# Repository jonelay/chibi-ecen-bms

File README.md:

# Chibi-ECEN-BMS: 7S Lithium-Ion Battery Management System

A 7-cell lithium-ion battery management system designed as a student project for EMEN 5830 (Fundamentals of Systems Engineering) at the University of Colorado Boulder in 2015.

<p align="center">
  
  &nbsp;&nbsp;&nbsp;
  
</p>

## Overview

This BMS was designed for an electric-assist recumbent tricycle with a focus on battery monitoring, safety, and data logging. The design used the ChibiOS operating system, and includes CAN bus communication, microSD data logging, and comprehensive fault detection.

⚠️ **Educational Prototype** - This was a graduate student learning project from 2015 focused on PCB layout techniques for power electronics. While the design is complete and boards were fabricated, this should be considered a learning exercise rather than a production-ready design. Firmware development was not released as part of the project.

## Key Features

- **7S Lithium-Ion Battery Monitoring** - LT6803-based cell voltage monitoring
- **STM32F303 Microcontroller** - ARM Cortex-M4 with floating-point unit
- **Safety Features** - Overcurrent, overvoltage, undervoltage, and thermal protection
- **CAN Bus Interface** - ADM3054 isolated CAN transceiver for vehicle communication
- **Data Logging** - microSD card storage for voltage, current, temperature data
- **Power Management** - LT3990 buck-boost converter for auxiliary power
- **Debug Interface** - JTAG programming and debugging support
- **User Feedback** - RGB status LED, two buttons for user input

## Technical Specifications

- **Battery Configuration**: 7S (7 cells in series)
- **Cell Chemistry**: 18650 Lithium-Ion (Samsung ICR18650-30B, 3000mAh)
- **Voltage Range**: 19.6V - 29.4V (2.8V - 4.2V per cell)
- **Microcontroller**: STM32F303CBT6 (ARM Cortex-M4, 48MHz, 128KB Flash)
- **Battery Monitor**: LT6803-1 (multicell battery stack monitor)
- **Communication**: CAN 2.0B, USB 2.0 (micro-B connector)
- **Data Logging**: microSD card (SPI interface)
- **PCB**: 4-layer board, approximately 100mm x 75mm

See [docs/specifications.md](docs/specifications.md) for complete specifications.

## Systems Engineering Process

This project followed a rigorous systems engineering methodology as taught in EMEN 5830:

1. **Requirements Development** - Stakeholder needs analysis, system requirements derivation
2. **Concept of Operations** - Use cases, operational scenarios, system interactions
3. **Functional Analysis** - 21 iterations of Functional Flow Block Diagrams (FFDB)
4. **Trade Studies** - Component selection based on cost, performance, availability
5. **Design** - Schematic capture, PCB layout, mechanical integration
6. **Testing** - Comprehensive test procedures and validation

The [analysis/](analysis/) directory contains the complete systems engineering documentation, including all 21 FFDB iterations showing the evolution of the design through failure mode analysis.

## Hardware Versions

### Version 1 (v01) - Manufactured & Tested
Version 1 was designed in February 2015, manufactured in March 2015, and tested as part of the course project. Complete gerber files, BOM, and test documentation are included.

- **Status**: Manufactured, assembled, and tested
- **Manufacturing Files**: Complete gerbers available in `hardware/bms-v01/gerbers/`
- **Documentation**: Full schematic, layout, BOM, and test results included

### Version 2 (v02) - Design Iteration
Version 2 was a design iteration that incorporated lessons learned from v01 testing, including corrections to the 8MHz crystal package and expanded AUX power traces. This version was never manufactured and the design files remain in the Eagle source directory.

## Repository Structure

```
chibi-ecen-bms/
├── hardware/              # Manufacturing-ready files (PDFs, gerbers, BOM)
│   └── bms-v01/          # Version 1 (manufactured)
├── design-source/         # Native design files
│   ├── eagle/            # Eagle CAD schematics and layouts
│   ├── cubemx/           # STM32 configuration files
│   └── mechanical/       # SolidWorks models and renders
├── docs/                  # Documentation
├── analysis/              # Systems engineering analysis
│   ├── requirements/     # Requirements documentation
│   ├── failure-analysis/ # FFDB diagrams (21 iterations)
│   ├── calculations/     # Battery and system calculations
│   ├── trade-studies/    # Component selection analysis
│   └── diagrams/         # System block diagrams
├── datasheets/           # Key component datasheets
├── media/                # Photos, renders, and presentation
└── testing/              # Test procedures and results
```

## Getting Started

### Manufacturing

To manufacture this board:

1. Review the [schematic](hardware/bms-v01/bms_v01_schematic.pdf) and [layout](hardware/bms-v01/bms_v01_layout.pdf)
2. Order PCBs using the [gerber files](hardware/bms-v01/gerbers/)
3. Order components from the [BOM](hardware/bms-v01/bms_v01_assembly_bom.csv)
4. Refer to the [test procedure](testing/test-procedure.pdf) for validation

### Modifying the Design

The source Eagle CAD files are in [design-source/eagle/](design-source/eagle/). The STM32 peripheral configuration can be modified using STM32CubeMX with the [.ioc file](design-source/cubemx/bms_v01.ioc).

## Documentation

- **[Specifications](docs/specifications.md)** - System requirements and performance specs
- **[Pinout](docs/pinout.md)** - Connector pinouts and signal definitions
- **[Hardware README](hardware/README.md)** - Manufacturing file details

## Known Issues

Version 1 has two known issues that were addressed in the v02 design:

1. **8MHz Crystal Package** - Incorrect footprint requires rework or substitution
2. **AUX Power Trace** - Undersized trace for auxiliary power distribution

Workarounds: The crystal issue can be resolved by hand-soldering the correct package or using an adapter. The power trace issue can be addressed by adding solder to thicken the trace or adding a parallel wire jumper.

## License

This project is released under the MIT License. See [LICENSE](LICENSE) for details.

Copyright (c) 2015 Jone Lay

You are free to use, modify, and distribute this design for any purpose, with attribution.

## Open Source Hardware

This project is open source hardware. The design files, manufacturing files, and documentation are freely available for educational and non-commercial use.

## Disclaimer

*This project is shared for educational purposes and as a portfolio piece. It was a graduate student project from 2015. While care was taken in the design and the hardware was successfully manufactured and tested, this is not a production-ready design. Use at your own risk. Battery management systems must be designed with extreme care for safety - this design is presented for educational purposes only.

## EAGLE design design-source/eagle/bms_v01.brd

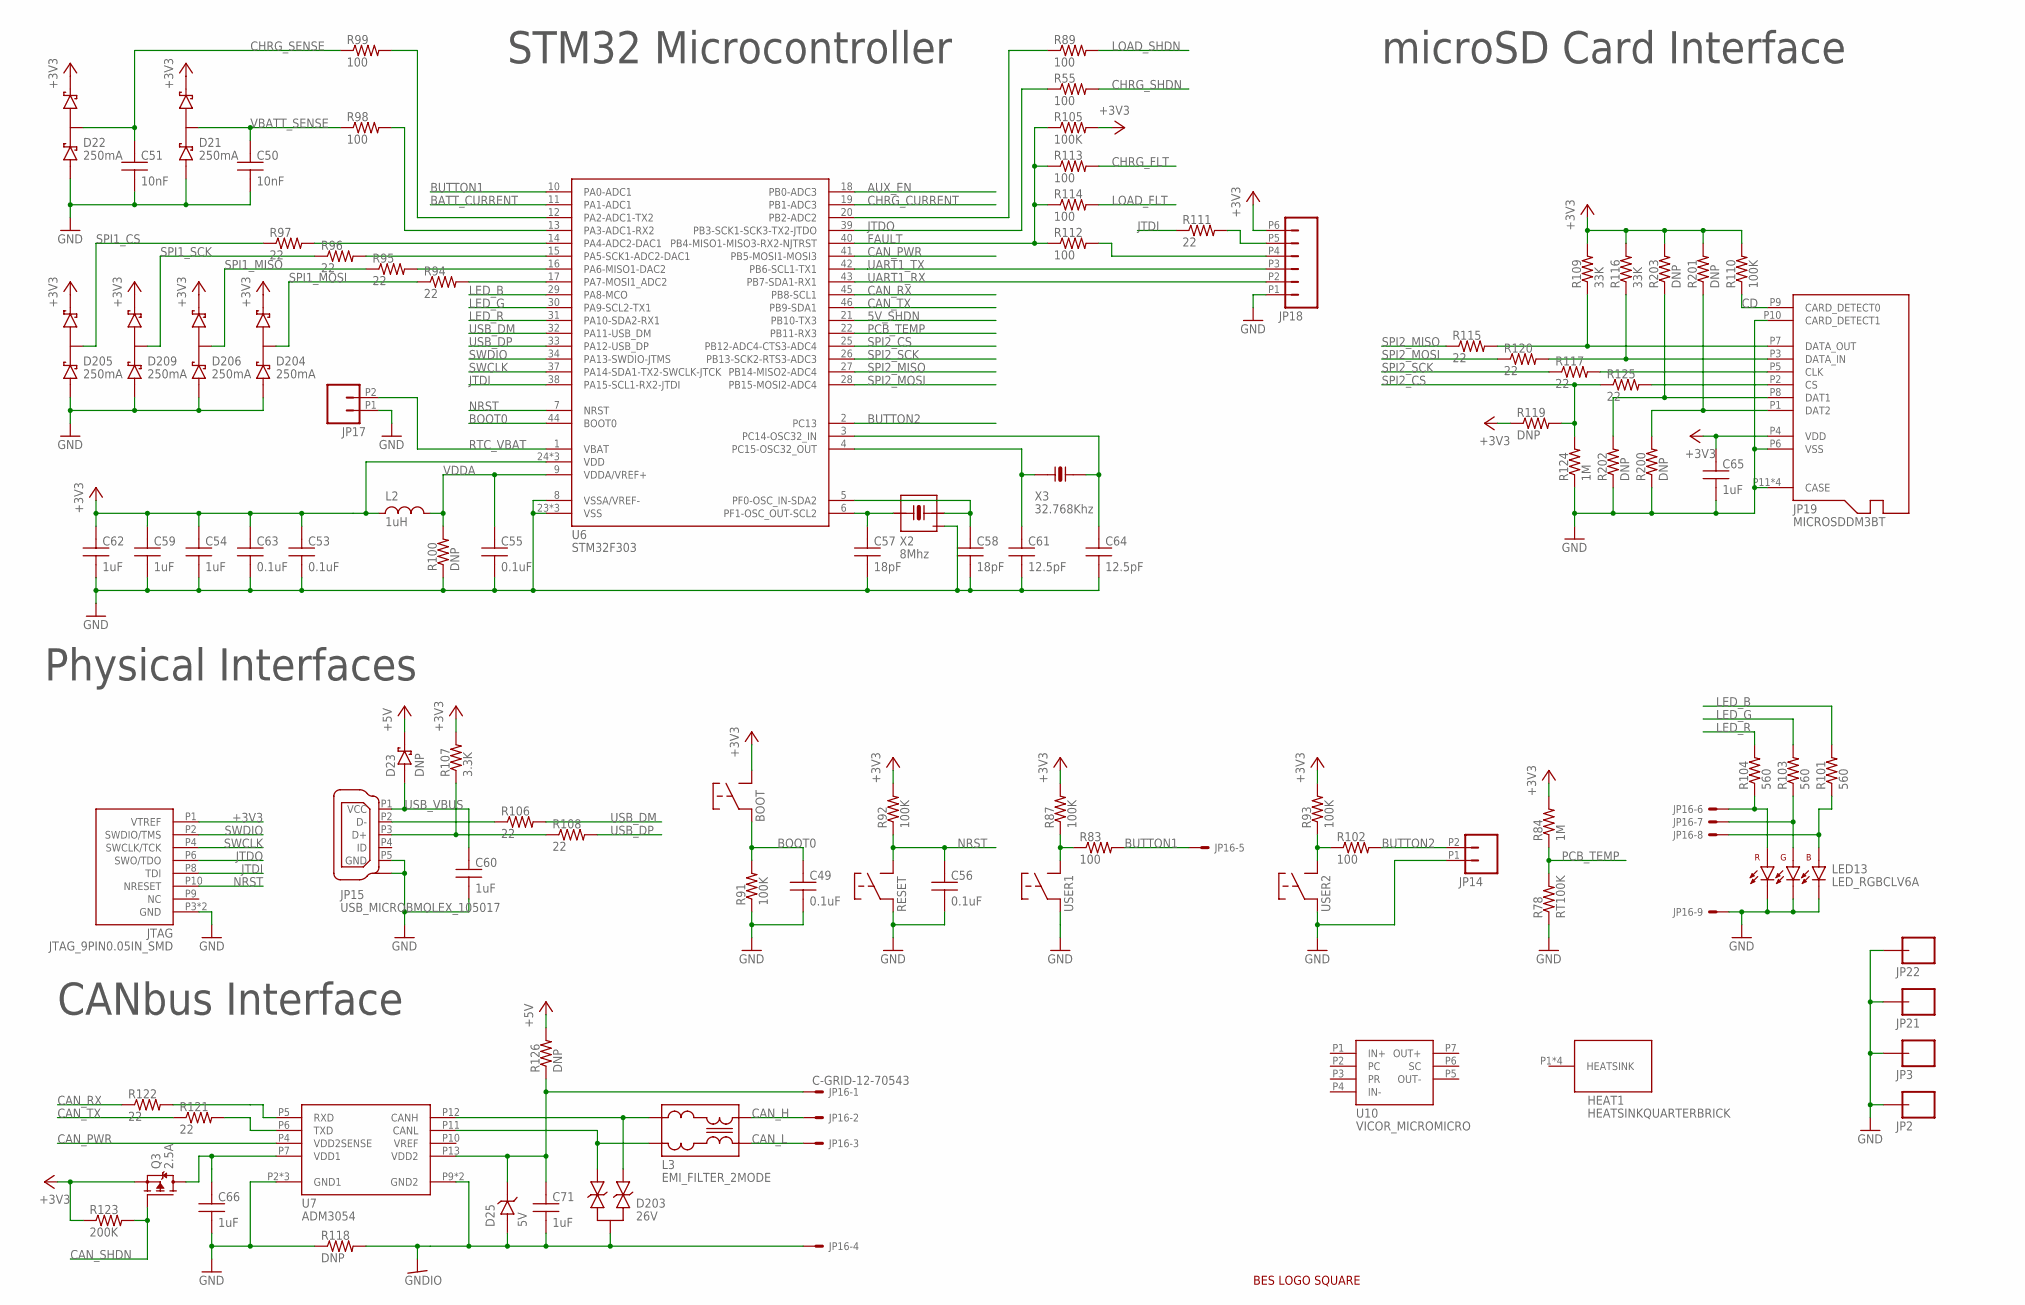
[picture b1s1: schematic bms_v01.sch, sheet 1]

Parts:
BOOT: SWITCH_MOMENTEVQP2; MOMENTARY_SW_EVQP2
C49, C53, C55, C56, C63: 0.1uF; 0603_SILK
C50, C51: 10nF; 0603_SILK
C54, C59, C60, C62, C65, C66, C71: 1uF; 0603_SILK
C57, C58: 18pF; 0603_SILK
C61, C64: 12.5pF; 0603_SILK
D21, D22, D204, D205, D206, D209: 250mA; SOT23
D23: DNP; SOT23
D25: 5V; SOT23
D203: 26V; SOT23
HEAT1: HEATSINKQUARTERBRICK; HEATSINK_BRICK_QUARTER
JP2, JP3, JP21, JP22: CONNECTOR-1PIN3.5MM; HOLE_3.5MM
JP14: HEADER-2PIN2MM; HEADER_2MM_2PIN
JP15: USB_MICROBMOLEX_105017; USB-MICRO-B-MOLEX_105017
JP16: C-GRID-12-70543; 70543-12
JP17: HEADER-2PIN0.05IN; HEADER-SMALL-2PIN00.05IN
JP18: HEADER-6PIN2MM; HEADER_2MM_6PIN
JP19: MICROSDDM3BT; MICROSD_DM3BT
JTAG: JTAG_9PIN0.05IN_SMD; JTAG_9PIN_0.05IN_SMD
L2: 1uH; 0603_SILK
L3: EMI_FILTER_2MODE; FILTER_EXC24CX
LED13: LED_RGBCLV6A; RGB_LED_CLV6A
LOGO1: LOGOSILK_0.325IN; LOGO_SILK_0.325IN
Q3: 2.5A; SOT23
R55, R83, R89, R98, R99, R102, R112, R113, R114: 100; 0603_SILK
R78: RT100K; 0603_SILK
R84, R124: 1M; 0603_SILK
R87, R91, R92, R93, R105, R110: 100K; 0603_SILK
R94, R95, R96, R97, R106, R108, R111, R115, R117, R120, R121, R122, R125: 22; 0603_SILK
R100, R118, R119, R126, R200, R201, R202, R203: DNP; 0603_SILK
R101, R103, R104: 560; 0603_SILK
R107: 3.3K; 0603_SILK
R109, R116: 33K; 0603_SILK
R123: 200K; 0603_SILK
RESET: SWITCH_MOMENTEVQP2; MOMENTARY_SW_EVQP2
U6: STM32F303; TQFP48
U7: ADM3054; SOIC-16_W_ANALOG
U10: VICOR_MICROMICRO; VICOR_QUARTER
USER1, USER2: SWITCH_MOMENTEVQP2; MOMENTARY_SW_EVQP2
X2: 8Mhz; ABRACOM_CLOCK
X3: 32.768Khz; ABS07

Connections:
5V_SHDN: U6.21 (PB10-TX3); also elsewhere on the board
+3V3: BOOT.P2, BOOT.P4 (P2), C53.P1 (1), C54.P1 (1), C59.P1 (1), C62.P1 (1), C63.P1 (1), C65.P1 (1), D21.2 (C), D22.2 (C), D204.2 (C), D205.2 (C), D206.2 (C), D209.2 (C), JP18.P6, JP19.P4 (VDD), JTAG.P1 (VTREF), L2.P1 (1), Q3.2 (S), R84.P2 (2), R87.P2 (2), R92.P2 (2), R93.P2 (2), R105.P2 (2), R107.P2 (2), R109.P2 (2), R110.P2 (2), R116.P2 (2), R119.P1 (1), R123.P1 (1), R201.P2 (2), R203.P2 (2), U6.24 (VDD), U6.36 (VDD), U6.48 (VDD); also elsewhere on the board
+5V: D23.3 (C), R126.P2 (2); also elsewhere on the board
AUX_EN: U6.18 (PB0-ADC3); also elsewhere on the board
BATT_CURRENT: U6.11 (PA1-ADC1); also elsewhere on the board
BOOT0: BOOT.P1, BOOT.P3 (P1), C49.P1 (1), R91.P2 (2), U6.44 (BOOT0)
BUTTON1: JP16.5, R83.P2 (2), U6.10 (PA0-ADC1)
BUTTON2: JP14.P2, R102.P2 (2), U6.2 (PC13)
CAN_H: JP16.2, L3.P4 (4)
CAN_L: JP16.3, L3.P3 (3)
CAN_PWR: U6.41 (PB5-MOSI1-MOSI3), U7.P4 (VDD2SENSE)
CAN_RX: R122.P1 (1), U6.45 (PB8-SCL1)
CAN_SHDN: Q3.1 (G), R123.P2 (2); also elsewhere on the board
CAN_TX: R121.P1 (1), U6.46 (PB9-SDA1)
CAN_VDD: C71.P1 (1), D25.3 (C), JP16.1, R126.P1 (1), U7.P13 (VDD2)
CD: JP19.P9 (CARD_DETECT0), R110.P1 (1)
CHRG_CURRENT: U6.19 (PB1-ADC3); also elsewhere on the board
CHRG_FLT: R113.P2 (2); also elsewhere on the board
CHRG_SENSE: C51.P1 (1), D22.3 (MID), R99.P1 (1); also elsewhere on the board
CHRG_SHDN: R55.P2 (2); also elsewhere on the board
FAULT: R105.P1 (1), R112.P1 (1), R113.P1 (1), R114.P1 (1), U6.40 (PB4-MISO1-MISO3-RX2-NJTRST)
GND: C49.P2 (2), C50.P2 (2), C51.P2 (2), C53.P2 (2), C54.P2 (2), C55.P2 (2), C56.P2 (2), C57.P2 (2), C58.P2 (2), C59.P2 (2), C60.P2 (2), C61.P2 (2), C62.P2 (2), C63.P2 (2), C64.P2 (2), C65.P2 (2), C66.P2 (2), D21.1 (A), D22.1 (A), D204.1 (A), D205.1 (A), D206.1 (A), D209.1 (A), JP2.P$1, JP3.P$1, JP14.P1, JP15.P5 (GND), JP15.PAD1 (CASE), JP15.PAD2 (CASE), JP15.PAD3 (CASE), JP15.PAD3-HOLE (CASE), JP15.PAD4 (CASE), JP15.PAD4-HOLE (CASE), JP15.THRUPAD1 (CASE), JP15.THRUPAD2 (CASE), JP16.9, JP17.P1, JP18.P1, JP19.P6 (VSS), JP19.P10 (CARD_DETECT1), JP19.P11 (CASE), JP19.P12 (CASE), JP19.P13 (CASE), JP19.P14 (CASE), JP21.P$1, JP22.P$1, JTAG.P3 (GND), JTAG.P5 (GND), LED13.1 (BC), LED13.2 (GC), LED13.3 (RC), R78.P1 (1), R91.P1 (1), R100.P1 (1), R118.P1 (1), R124.P1 (1), R200.P1 (1), R202.P1 (1), RESET.P1, RESET.P3 (P1), U6.8 (VSSA/VREF-), U6.23 (VSS), U6.35 (VSS), U6.47 (VSS), U7.P2 (GND1), U7.P3 (GND1), U7.P8 (GND1), USER1.P1, USER1.P3 (P1), USER2.P1, USER2.P3 (P1), X2.2 (CASE), X2.4 (CASE); also elsewhere on the board
GNDIO: C71.P2 (2), D25.1 (A), D203.3 (C1), JP16.4, R118.P2 (2), U7.P9 (GND2), U7.P16 (GND2)
JTDI: JTAG.P8 (TDI), R111.P1 (1), U6.38 (PA15-SCL1-RX2-JTDI)
JTDO: JTAG.P6 (SWO/TDO), R55.P1 (1), U6.39 (PB3-SCK1-SCK3-TX2-JTDO)
LED_B: R101.P2 (2), U6.29 (PA8-MCO)
LED_G: R103.P2 (2), U6.30 (PA9-SCL2-TX1)
LED_R: R104.P2 (2), U6.31 (PA10-SDA2-RX1)
LOAD_FLT: R114.P2 (2); also elsewhere on the board
LOAD_SHDN: R89.P2 (2); also elsewhere on the board
unnamed: C66.P1 (1), Q3.3 (D), U7.P7 (VDD1)
unnamed: D203.1 (A), L3.P2 (2), U7.P11 (CANL)
unnamed: R99.P2 (2), U6.12 (PA2-ADC1-TX2)
unnamed: R83.P1 (1), R87.P1 (1), USER1.P2, USER1.P4 (P2)
unnamed: JP15.P2 (D-), R106.P1 (1)
unnamed: R93.P1 (1), R102.P1 (1), USER2.P2, USER2.P4 (P2)
unnamed: R89.P1 (1), U6.20 (PB2-ADC2)
unnamed: R98.P2 (2), U6.13 (PA3-ADC1-RX2)
unnamed: C58.P1 (1), U6.5 (PF0-OSC_IN-SDA2), X2.3 (3A)
unnamed: JP15.P3 (D+), R107.P1 (1), R108.P1 (1)
unnamed: R94.P2 (2), U6.17 (PA7-MOSI1_ADC2)
unnamed: R95.P2 (2), U6.16 (PA6-MISO1-DAC2)
unnamed: C57.P1 (1), U6.6 (PF1-OSC_OUT-SCL2), X2.1 (1A)
unnamed: R96.P2 (2), U6.15 (PA5-SCK1-ADC2-DAC1)
unnamed: JP19.P1 (DAT2), R200.P2 (2), R201.P1 (1)
unnamed: JP19.P8 (DAT1), R202.P2 (2), R203.P1 (1)
unnamed: JP19.P3 (DATA_IN), R116.P1 (1), R120.P2 (2)
unnamed: JP19.P7 (DATA_OUT), R109.P1 (1), R115.P2 (2)
unnamed: D203.2 (A1), L3.P1 (1), U7.P12 (CANH)
unnamed: R121.P2 (2), U7.P6 (TXD)
unnamed: R122.P2 (2), U7.P5 (RXD)
unnamed: R97.P2 (2), U6.14 (PA4-ADC2-DAC1)
unnamed: C61.P1 (1), U6.4 (PC15-OSC32_OUT), X3.P1 (1A)
unnamed: C64.P1 (1), U6.3 (PC14-OSC32_IN), X3.P2 (3A)
unnamed: JP18.P4, R112.P2 (2)
unnamed: JP18.P5, R111.P2 (2)
unnamed: JP19.P5 (CLK), R117.P2 (2)
unnamed: JP19.P2 (CS), R125.P2 (2)
unnamed: JP16.6, LED13.4 (RA), R104.P1 (1)
unnamed: JP16.7, LED13.5 (GA), R103.P1 (1)
unnamed: JP16.8, LED13.6 (BA), R101.P1 (1)
NRST: C56.P1 (1), JTAG.P10 (NRESET), R92.P1 (1), RESET.P2, RESET.P4 (P2), U6.7 (NRST)
PCB_TEMP: R78.P2 (2), R84.P1 (1), U6.22 (PB11-RX3)
RTC_VBAT: JP17.P2, U6.1 (VBAT)
SPI1_CS: D205.3 (MID), R97.P1 (1); also elsewhere on the board
SPI1_MISO: D206.3 (MID), R95.P1 (1); also elsewhere on the board
SPI1_MOSI: D204.3 (MID), R94.P1 (1); also elsewhere on the board
SPI1_SCK: D209.3 (MID), R96.P1 (1); also elsewhere on the board
SPI2_CS: R119.P2 (2), R124.P2 (2), R125.P1 (1), U6.25 (PB12-ADC4-CTS3-ADC4)
SPI2_MISO: R115.P1 (1), U6.27 (PB14-MISO2-ADC4)
SPI2_MOSI: R120.P1 (1), U6.28 (PB15-MOSI2-ADC4)
SPI2_SCK: R117.P1 (1), U6.26 (PB13-SCK2-RTS3-ADC3)
SWCLK: JTAG.P4 (SWCLK/TCK), U6.37 (PA14-SDA1-TX2-SWCLK-JTCK)
SWDIO: JTAG.P2 (SWDIO/TMS), U6.34 (PA13-SWDIO-JTMS)
UART1_RX: JP18.P2, U6.43 (PB7-SDA1-RX1)
UART1_TX: JP18.P3, U6.42 (PB6-SCL1-TX1)
USB_DM: R106.P2 (2), U6.32 (PA11-USB_DM)
USB_DP: R108.P2 (2), U6.33 (PA12-USB_DP)
USB_VBUS: C60.P1 (1), D23.1 (A), JP15.P1 (VCC)
VBATT_SENSE: C50.P1 (1), D21.3 (MID), R98.P1 (1); also elsewhere on the board
VDDA: C55.P1 (1), L2.P2 (2), R100.P2 (2), U6.9 (VDDA/VREF+)

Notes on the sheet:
CANbus Interface
STM32 Microcontroller
microSD Card Interface
Physical Interfaces

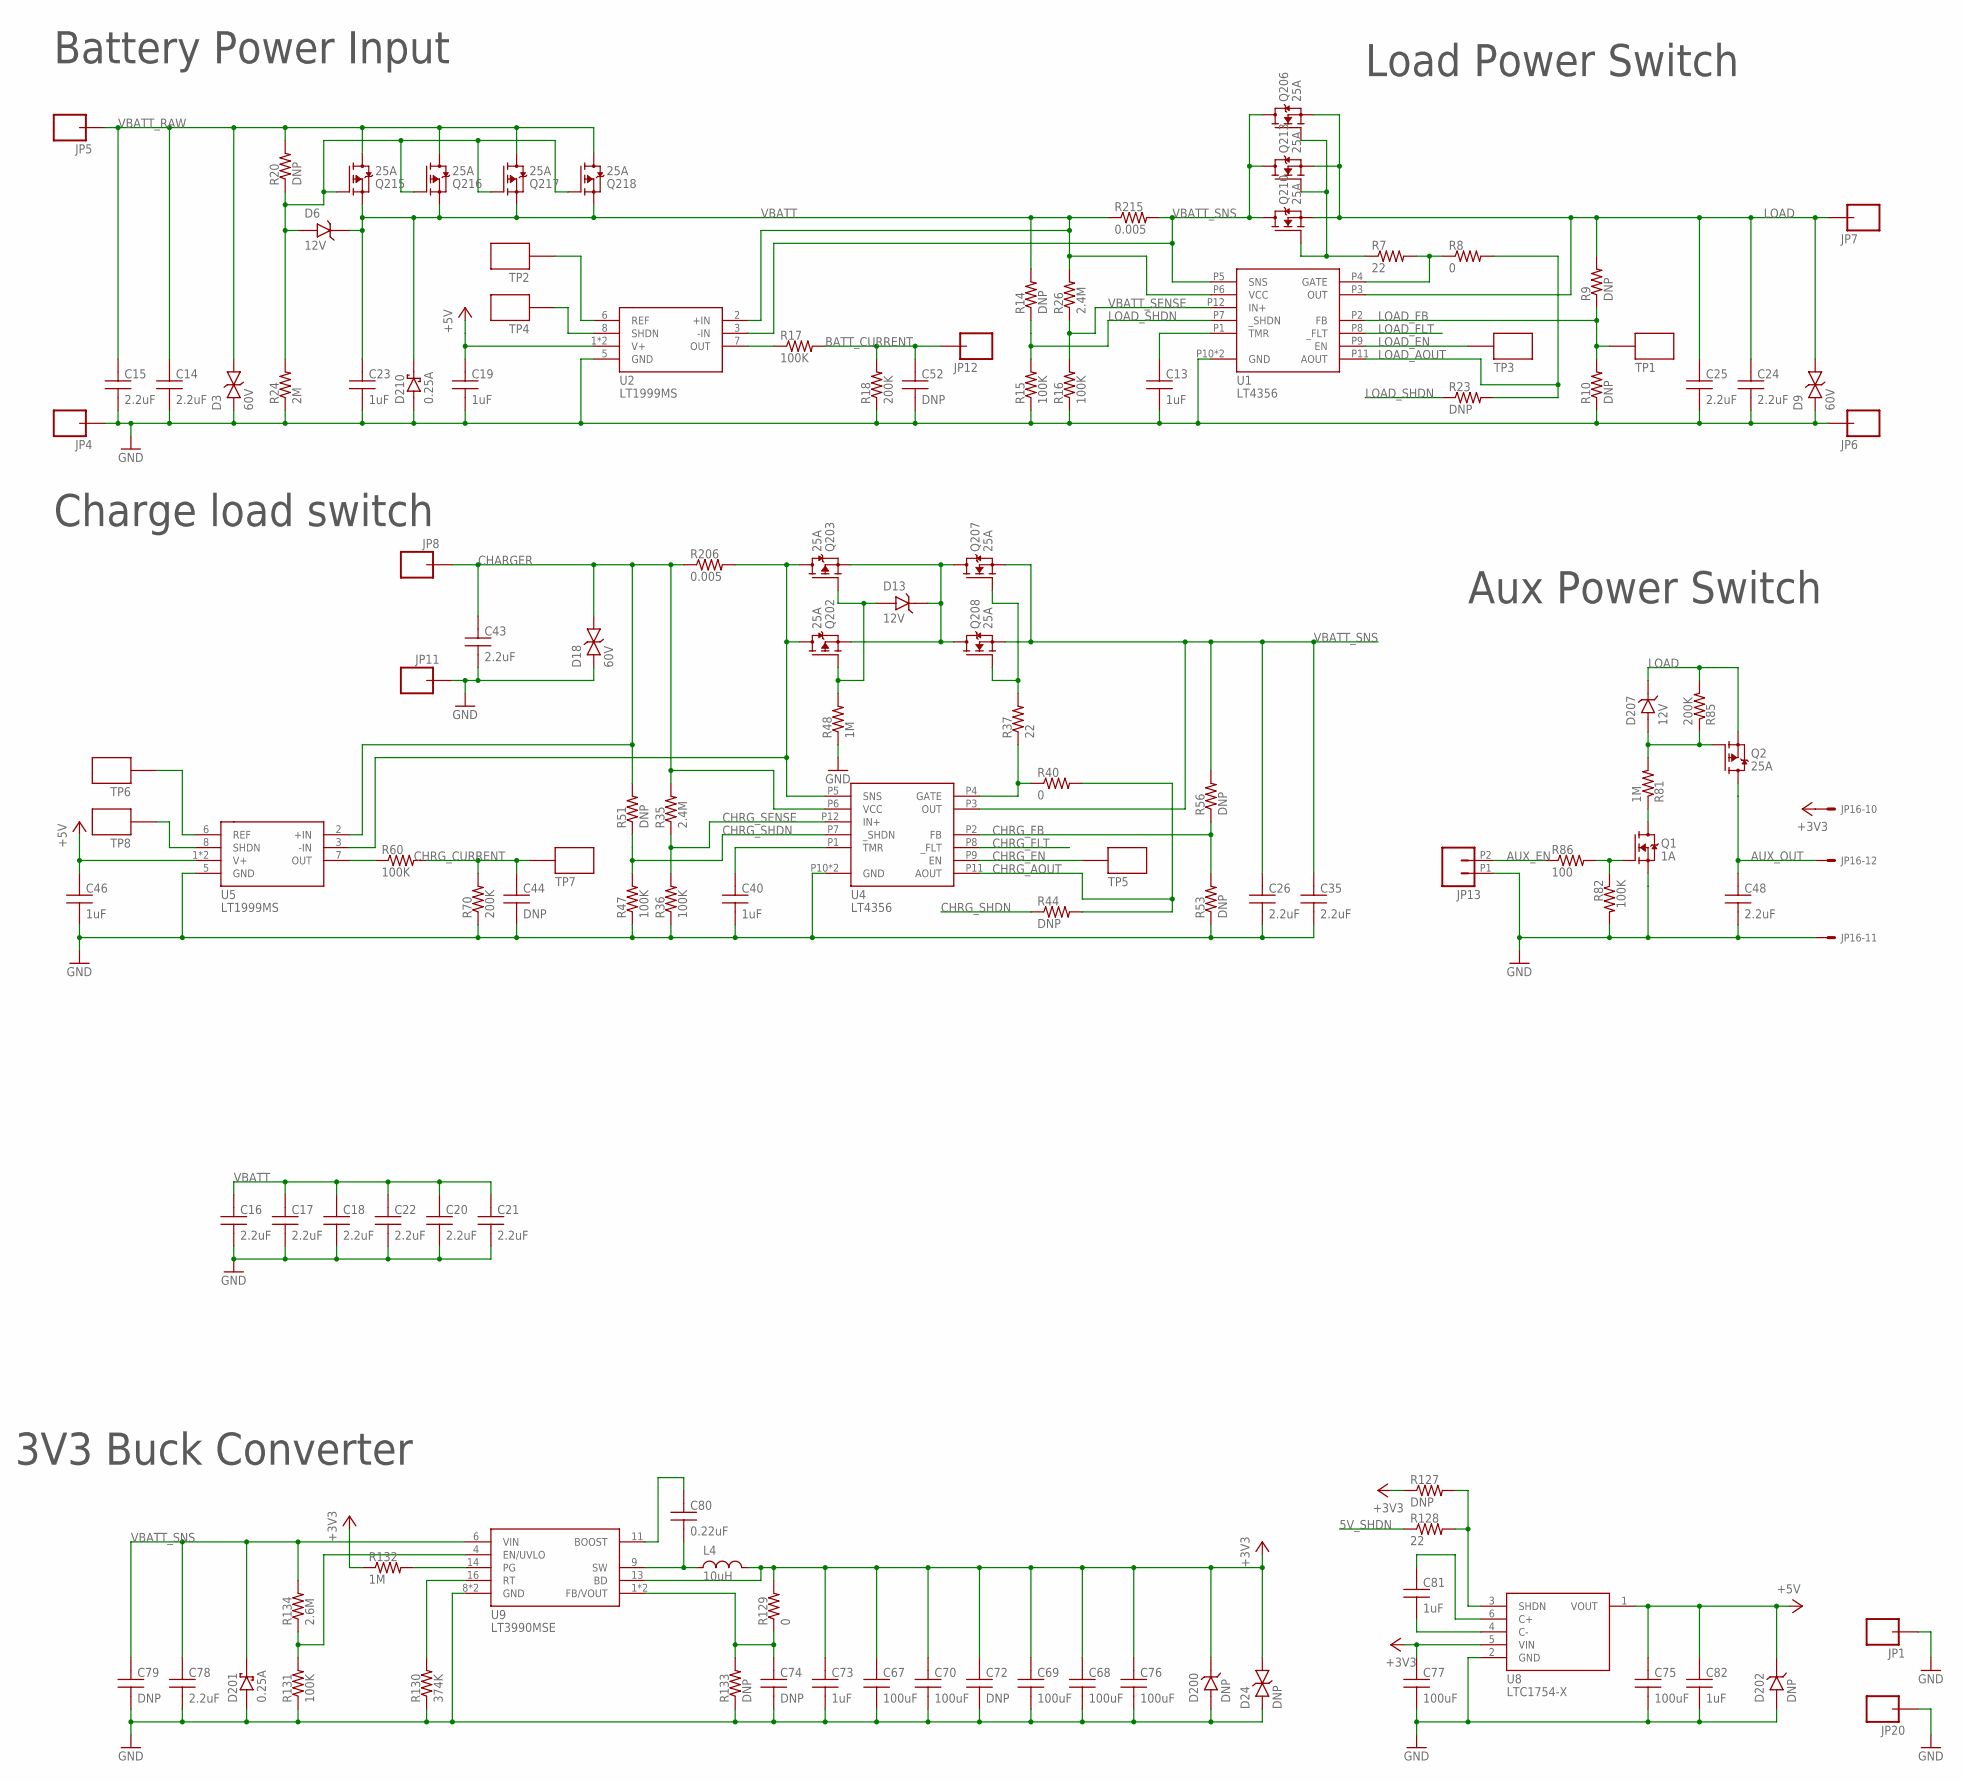
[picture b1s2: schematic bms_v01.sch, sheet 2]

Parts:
C13, C19, C23, C40, C46, C73, C81, C82: 1uF; 0603_SILK
C14, C15, C16, C17, C18, C20, C21, C22, C24, C25, C26, C35, C43, C48, C78: 2.2uF; 1210_SILK
C44, C52, C72, C74, C79: DNP; 0603_SILK
C67, C68, C69, C70, C75, C76, C77: 100uF; 1206_SILK
C80: 0.22uF; 0603_SILK
D3, D9, D18: 60V; SMC
D6, D13, D207: 12V; SOT23
D24: DNP; SMA
D200, D202: DNP; SOT23
D201, D210: 0.25A; SOT23
JP1, JP20: HEADER-1PIN0.036IN; HEADER-SMALL-1PIN-0.036IN
JP4, JP5, JP6, JP7, JP8, JP11: CONNECTOR-1PIN3MM; HOLE_3MM
JP12: HEADER-1PIN0.02IN; HEADER-SMALL-1PIN-0.02IN
JP13: HEADER-2PIN2MM; HEADER_2MM_2PIN
JP16: C-GRID-12-70543; 70543-12
L4: 10uH; INDUCTOR_RL895
Q1: 1A; SOT23
Q2, Q202, Q203, Q206, Q207, Q208, Q210, Q213, Q215, Q216, Q217, Q218: 25A; POWERPAK_SO-8_SINGLE
R7: 22; 0805_SILK
R8: 0; 0805_SILK
R9, R10, R14, R20, R44, R51, R53, R56, R127, R133: DNP; 0603_SILK
R15, R16, R17, R36, R47, R60, R82, R131: 100K; 0603_SILK
R18, R70, R85: 200K; 0603_SILK
R23: DNP; 0805_SILK
R24: 2M; 0603_SILK
R26, R35: 2.4M; 0603_SILK
R37, R128: 22; 0603_SILK
R40, R129: 0; 0603_SILK
R48, R81, R132: 1M; 0603_SILK
R86: 100; 0603_SILK
R130: 374K; 0603_SILK
R134: 2.6M; 0603_SILK
R206, R215: 0.005; 2725_SILK
TP1, TP2, TP4, TP6, TP7, TP8: TEST_POINT0.036IN; TEST_POINT_0.036IN
TP3, TP5: TEST_POINT0.025IN; TEST_POINT_0.025IN
U1, U4: LT4356; DFN12
U2, U5: LT1999MS; MSOP-8_LT
U8: LTC1754-X; SOT23-6
U9: LT3990MSE; 17_MSOP

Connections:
5V_SHDN: R128.P1 (1); also elsewhere on the board
+3V3: C67.P1 (1), C68.P1 (1), C69.P1 (1), C70.P1 (1), C72.P1 (1), C73.P1 (1), C76.P1 (1), C77.P1 (1), D24.C, D200.3 (C), JP16.10, L4.P2 (2), R127.P1 (1), R129.P2 (2), R132.P1 (1), U8.5 (VIN), U9.13 (BD); also elsewhere on the board
+5V: C19.P1 (1), C46.P1 (1), C75.P1 (1), C82.P1 (1), D202.3 (C), U2.1 (V+), U2.4 (V+), U5.1 (V+), U5.4 (V+), U8.1 (VOUT); also elsewhere on the board
AUX_EN: JP13.P2, R86.P1 (1); also elsewhere on the board
AUX_OUT: C48.1, JP16.12, Q2.5D (D), Q2.6D (D), Q2.7D (D), Q2.8D (D), Q2.9D (D)
BATT_CURRENT: C52.P1 (1), JP12.P1, R17.P2 (2), R18.P2 (2); also elsewhere on the board
CHARGER: C43.1, D18.C, JP8.P1, R35.P2 (2), R51.P2 (2), R206.P1 (1), U4.P6 (VCC), U5.2 (+IN)
CHARGER_SENSE: Q202.5D (D), Q202.6D (D), Q202.7D (D), Q202.8D (D), Q202.9D (D), Q203.5D (D), Q203.6D (D), Q203.7D (D), Q203.8D (D), Q203.9D (D), R206.P2 (2), U4.P5 (SNS), U5.3 (-IN)
CHRG_AOUT: R40.P2 (2), R44.P2 (2), U4.P11 (AOUT)
CHRG_CURRENT: C44.P1 (1), R60.P2 (2), R70.P2 (2), TP7.P1; also elsewhere on the board
CHRG_EN: TP5.P1, U4.P9 (EN)
CHRG_FB: R53.P2 (2), R56.P1 (1), U4.P2 (FB)
CHRG_FLT: U4.P8 (_FLT); also elsewhere on the board
CHRG_SENSE: R35.P1 (1), R36.P2 (2), U4.P12 (IN+); also elsewhere on the board
CHRG_SHDN: R44.P1 (1), R47.P2 (2), R51.P1 (1), U4.P7 (_SHDN); also elsewhere on the board
GND: C13.P2 (2), C14.2, C15.2, C16.2, C17.2, C18.2, C19.P2 (2), C20.2, C21.2, C22.2, C23.P2 (2), C24.2, C25.2, C26.2, C35.2, C40.P2 (2), C43.2, C44.P2 (2), C46.P2 (2), C48.2, C52.P2 (2), C67.P2 (2), C68.P2 (2), C69.P2 (2), C70.P2 (2), C72.P2 (2), C73.P2 (2), C74.P2 (2), C75.P2 (2), C76.P2 (2), C77.P2 (2), C78.2, C79.P2 (2), C82.P2 (2), D3.A, D9.A, D18.A, D24.A, D200.1 (A), D201.1 (A), D202.1 (A), D210.1 (A), JP1.P1, JP4.P1, JP6.P1, JP11.P1, JP13.P1, JP16.11, JP20.P1, Q1.2 (S), R10.P1 (1), R15.P1 (1), R16.P1 (1), R18.P1 (1), R24.P1 (1), R36.P1 (1), R47.P1 (1), R48.P1 (1), R53.P1 (1), R70.P1 (1), R82.P2 (2), R130.P1 (1), R131.P1 (1), R133.P1 (1), U1.P10 (GND), U1.TAB (GND), U2.5 (GND), U4.P10 (GND), U4.TAB (GND), U5.5 (GND), U8.2 (GND), U9.8 (GND), U9.17 (GND); also elsewhere on the board
LOAD: C24.1, C25.1, D9.C, D207.3 (C), JP7.P1, Q2.1S (S), Q2.2S (S), Q2.3S (S), Q206.1S (S), Q206.2S (S), Q206.3S (S), Q210.1S (S), Q210.2S (S), Q210.3S (S), Q213.1S (S), Q213.2S (S), Q213.3S (S), R9.P2 (2), R85.P2 (2), U1.P3 (OUT)
LOAD_AOUT: R8.P2 (2), R23.P2 (2), U1.P11 (AOUT)
LOAD_EN: TP3.P1, U1.P9 (EN)
LOAD_FB: R9.P1 (1), R10.P2 (2), TP1.P1, U1.P2 (FB)
LOAD_FLT: U1.P8 (_FLT); also elsewhere on the board
LOAD_SHDN: R14.P1 (1), R15.P2 (2), R23.P1 (1), U1.P7 (_SHDN); also elsewhere on the board
unnamed: C80.P2 (2), L4.P1 (1), U9.9 (SW)
unnamed: R60.P1 (1), U5.7 (OUT)
unnamed: R131.P2 (2), R134.P1 (1), U9.4 (EN/UVLO)
unnamed: R132.P2 (2), U9.14 (PG)
unnamed: R127.P2 (2), R128.P2 (2), U8.3 (SHDN)
unnamed: C40.P1 (1), U4.P1 (TMR)
unnamed: Q207.4G (G), Q208.4G (G), R37.P2 (2)
unnamed: R37.P1 (1), R40.P1 (1), U4.P4 (GATE)
unnamed: Q1.1 (G), R82.P1 (1), R86.P2 (2)
unnamed: C13.P1 (1), U1.P1 (TMR)
unnamed: D207.1 (A), Q2.4G (G), R81.P2 (2), R85.P1 (1)
unnamed: C80.P1 (1), U9.11 (BOOST)
unnamed: Q1.3 (D), R81.P1 (1)
unnamed: TP6.P1, U5.6 (REF)
unnamed: R130.P2 (2), U9.16 (RT)
unnamed: R17.P1 (1), U2.7 (OUT)
unnamed: Q206.4G (G), Q210.4G (G), Q213.4G (G), R7.P1 (1)
unnamed: TP2.P1, U2.6 (REF)
unnamed: R7.P2 (2), R8.P1 (1), U1.P4 (GATE)
unnamed: TP8.P1, U5.8 (SHDN)
unnamed: TP4.P1, U2.8 (SHDN)
unnamed: D13.1 (A), Q202.4G (G), Q203.4G (G), R48.P2 (2)
unnamed: C74.P1 (1), R129.P1 (1), R133.P2 (2), U9.1 (FB/VOUT), U9.2 (FB/VOUT)
unnamed: D6.1 (A), Q215.4G (G), Q216.4G (G), Q217.4G (G), Q218.4G (G), R20.P1 (1), R24.P2 (2)
unnamed: C81.P2 (2), U8.4 (C-)
unnamed: C81.P1 (1), U8.6 (C+)
VBATT: C16.1, C17.1, C18.1, C20.1, C21.1, C22.1, C23.P1 (1), D6.3 (C), D210.3 (C), Q215.1S (S), Q215.2S (S), Q215.3S (S), Q216.1S (S), Q216.2S (S), Q216.3S (S), Q217.1S (S), Q217.2S (S), Q217.3S (S), Q218.1S (S), Q218.2S (S), Q218.3S (S), R14.P2 (2), R26.P2 (2), R215.P1 (1), U1.P6 (VCC), U2.2 (+IN)
VBATT_RAW: C14.1, C15.1, D3.C, JP5.P1, Q215.5D (D), Q215.6D (D), Q215.7D (D), Q215.8D (D), Q215.9D (D), Q216.5D (D), Q216.6D (D), Q216.7D (D), Q216.8D (D), Q216.9D (D), Q217.5D (D), Q217.6D (D), Q217.7D (D), Q217.8D (D), Q217.9D (D), Q218.5D (D), Q218.6D (D), Q218.7D (D), Q218.8D (D), Q218.9D (D), R20.P2 (2)
VBATT_SENSE: R16.P2 (2), R26.P1 (1), U1.P12 (IN+); also elsewhere on the board
VBATT_SNS: C26.1, C35.1, C78.1, C79.P1 (1), D201.3 (C), Q206.5D (D), Q206.6D (D), Q206.7D (D), Q206.8D (D), Q206.9D (D), Q207.1S (S), Q207.2S (S), Q207.3S (S), Q208.1S (S), Q208.2S (S), Q208.3S (S), Q210.5D (D), Q210.6D (D), Q210.7D (D), Q210.8D (D), Q210.9D (D), Q213.5D (D), Q213.6D (D), Q213.7D (D), Q213.8D (D), Q213.9D (D), R56.P2 (2), R134.P2 (2), R215.P2 (2), U1.P5 (SNS), U2.3 (-IN), U4.P3 (OUT), U9.6 (VIN)
VCHARGER_SENSE: D13.3 (C), Q202.1S (S), Q202.2S (S), Q202.3S (S), Q203.1S (S), Q203.2S (S), Q203.3S (S), Q207.5D (D), Q207.6D (D), Q207.7D (D), Q207.8D (D), Q207.9D (D), Q208.5D (D), Q208.6D (D), Q208.7D (D), Q208.8D (D), Q208.9D (D)

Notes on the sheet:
Battery Power Input
3V3 Buck Converter
Charge load switch
Load Power Switch
Aux Power Switch

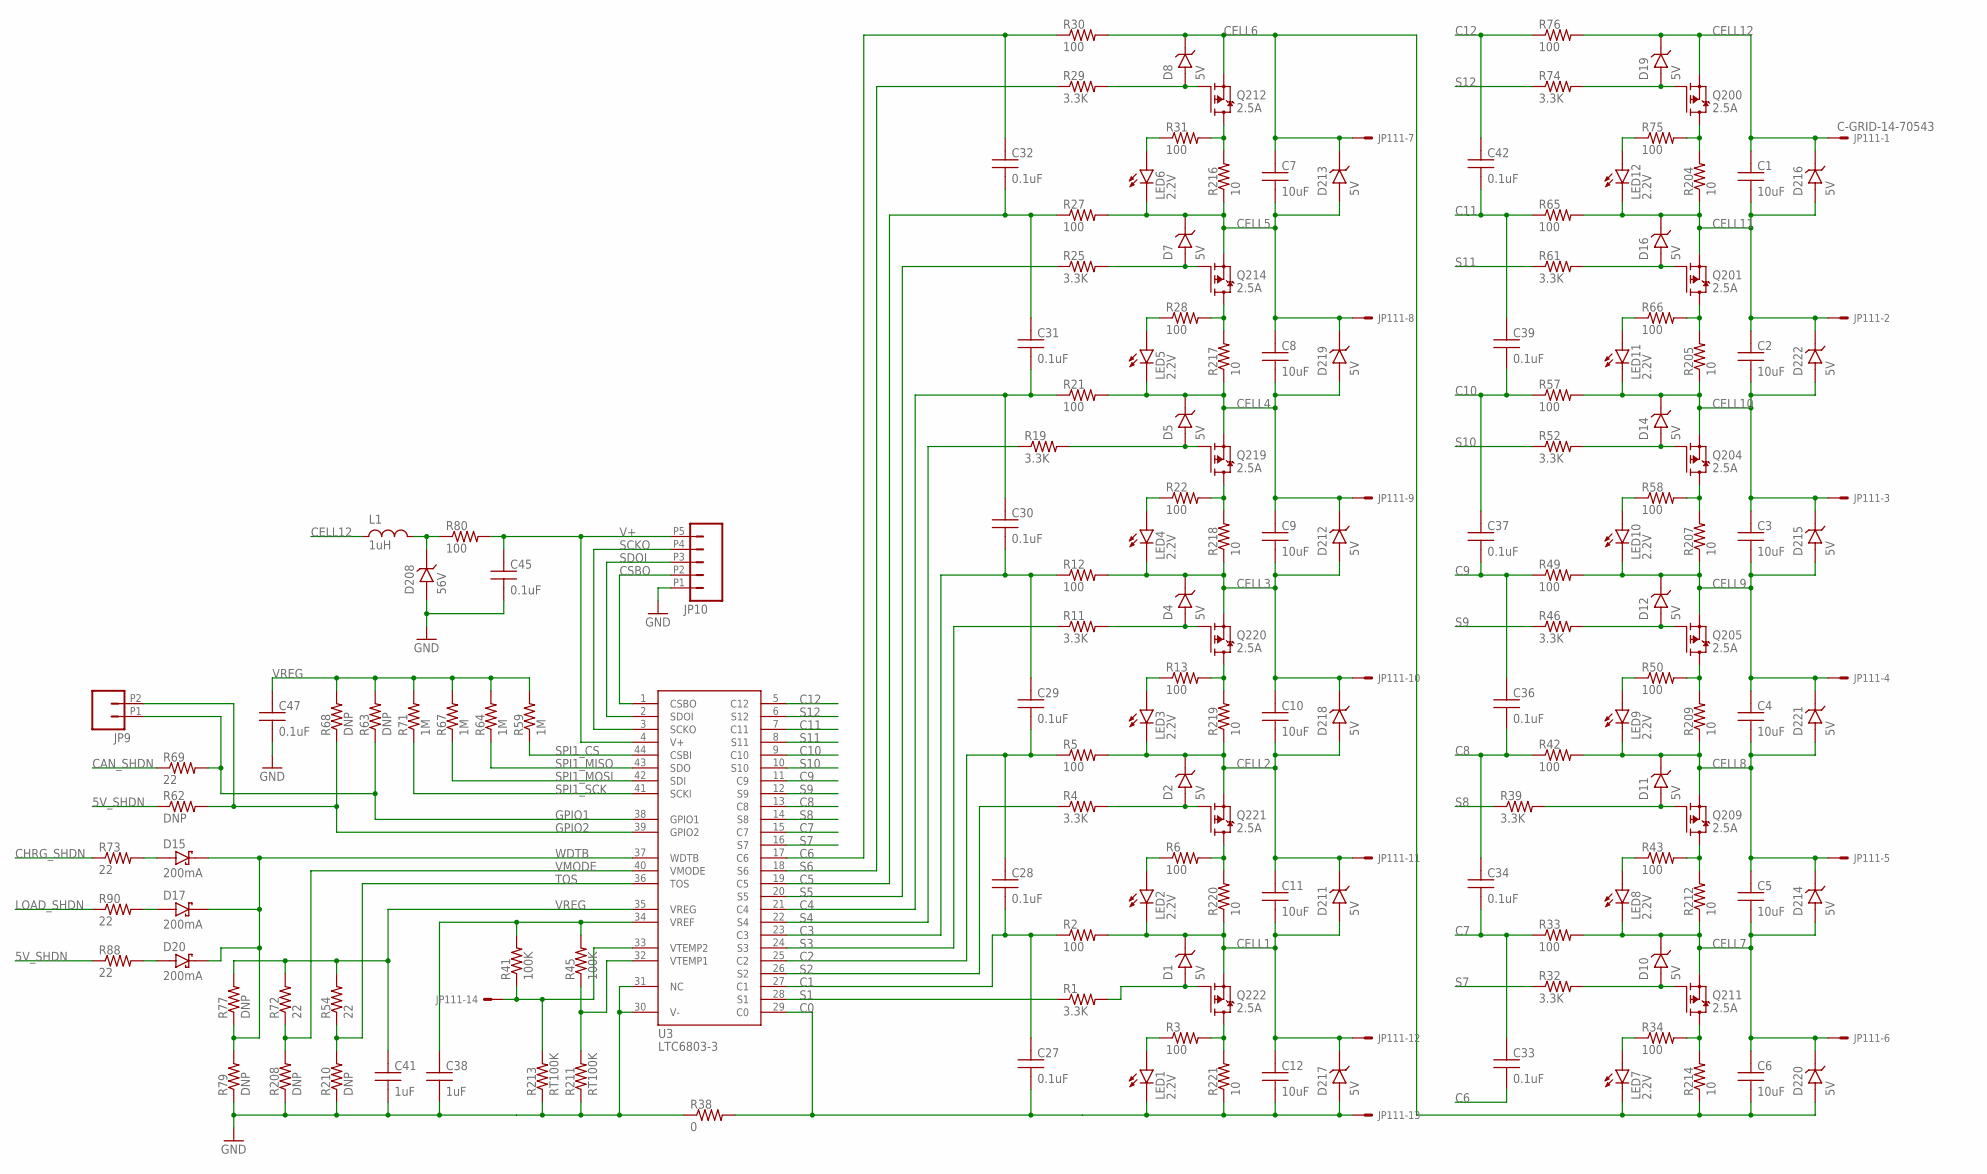
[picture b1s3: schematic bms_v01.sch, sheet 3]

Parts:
C1, C2, C3, C4, C5, C6, C7, C8, C9, C10, C11, C12: 10uF; 1206_SILK
C27, C28, C29, C30, C31, C32, C33, C34, C36, C37, C39, C42, C45, C47: 0.1uF; 0603_SILK
C38, C41: 1uF; 0603_SILK
D1, D2, D4, D5, D7, D8, D10, D11, D12, D14, D16, D19, D211, D212, D213, D214, D215, D216, D217, D218, D219, D220, D221, D222: 5V; SOT23
D15, D17, D20: 200mA; SOT23
D208: 56V; SOT23
JP9: HEADER-2PIN0.05IN; HEADER-SMALL-2PIN00.05IN
JP10: HEADER-5PIN2MM; HEADER_2MM_5PIN
JP111: C-GRID-14-70543; 70543-14
L1: 1uH; 0603_SILK
LED1, LED2, LED3, LED4, LED5, LED6, LED7, LED8, LED9, LED10, LED11, LED12: 2.2V; LED_0603
Q200, Q201, Q204, Q205, Q209, Q211, Q212, Q214, Q219, Q220, Q221, Q222: 2.5A; SOT23
R1, R4, R11, R19, R25, R29, R32, R39, R46, R52, R61, R74: 3.3K; 0603_SILK
R2, R3, R5, R6, R12, R13, R21, R22, R27, R28, R30, R31, R33, R34, R42, R43, R49, R50, R57, R58, R65, R66, R75, R76, R80: 100; 0603_SILK
R38: 0; 0603_SILK
R41, R45: 100K; 0603_SILK
R54, R69, R72, R73, R88, R90: 22; 0603_SILK
R59, R64, R67, R71: 1M; 0603_SILK
R62, R63, R68, R77, R79, R208, R210: DNP; 0603_SILK
R204, R205, R207, R209, R212, R214, R216, R217, R218, R219, R220, R221: 10; 2512_SILK
R211, R213: RT100K; 0603_SILK
U3: LTC6803-3; SSOP44

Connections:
5V_SHDN: R62.P1 (1), R88.P1 (1); also elsewhere on the board
C0: C12.P2 (2), C27.P2 (2), D217.1 (A), JP111.13, LED1.2 (C), R38.P2 (2), R221.1, U3.29 (C0)
C1: C27.P1 (1), C28.P2 (2), R2.P1 (1), U3.27 (C1)
C2: C28.P1 (1), C29.P2 (2), R5.P1 (1), U3.25 (C2)
C3: C29.P1 (1), C30.P2 (2), R12.P1 (1), U3.23 (C3)
C4: C30.P1 (1), C31.P2 (2), R21.P1 (1), U3.21 (C4)
C5: C31.P1 (1), C32.P2 (2), R27.P1 (1), U3.19 (C5)
C6: C32.P1 (1), C33.P2 (2), R30.P1 (1), U3.17 (C6)
C7: C33.P1 (1), C34.P2 (2), R33.P1 (1), U3.15 (C7)
C8: C34.P1 (1), C36.P2 (2), R42.P1 (1), U3.13 (C8)
C9: C36.P1 (1), C37.P2 (2), R49.P1 (1), U3.11 (C9)
C10: C37.P1 (1), C39.P2 (2), R57.P1 (1), U3.9 (C10)
C11: C39.P1 (1), C42.P2 (2), R65.P1 (1), U3.7 (C11)
C12: C42.P1 (1), R76.P1 (1), U3.5 (C12)
CAN_SHDN: R69.P1 (1); also elsewhere on the board
CELL1: C11.P2 (2), C12.P1 (1), D1.3 (C), D211.1 (A), D217.3 (C), JP111.12, LED2.2 (C), Q222.2 (S), R2.P2 (2), R220.1
CELL2: C10.P2 (2), C11.P1 (1), D2.3 (C), D211.3 (C), D218.1 (A), JP111.11, LED3.2 (C), Q221.2 (S), R5.P2 (2), R219.1
CELL3: C9.P2 (2), C10.P1 (1), D4.3 (C), D212.1 (A), D218.3 (C), JP111.10, LED4.2 (C), Q220.2 (S), R12.P2 (2), R218.1
CELL4: C8.P2 (2), C9.P1 (1), D5.3 (C), D212.3 (C), D219.1 (A), JP111.9, LED5.2 (C), Q219.2 (S), R21.P2 (2), R217.1
CELL5: C7.P2 (2), C8.P1 (1), D7.3 (C), D213.1 (A), D219.3 (C), JP111.8, LED6.2 (C), Q214.2 (S), R27.P2 (2), R216.1
CELL6: C6.P2 (2), C7.P1 (1), D8.3 (C), D213.3 (C), D220.1 (A), JP111.7, LED7.2 (C), Q212.2 (S), R30.P2 (2), R214.1
CELL7: C5.P2 (2), C6.P1 (1), D10.3 (C), D214.1 (A), D220.3 (C), JP111.6, LED8.2 (C), Q211.2 (S), R33.P2 (2), R212.1
CELL8: C4.P2 (2), C5.P1 (1), D11.3 (C), D214.3 (C), D221.1 (A), JP111.5, LED9.2 (C), Q209.2 (S), R42.P2 (2), R209.1
CELL9: C3.P2 (2), C4.P1 (1), D12.3 (C), D215.1 (A), D221.3 (C), JP111.4, LED10.2 (C), Q205.2 (S), R49.P2 (2), R207.1
CELL10: C2.P2 (2), C3.P1 (1), D14.3 (C), D215.3 (C), D222.1 (A), JP111.3, LED11.2 (C), Q204.2 (S), R57.P2 (2), R205.1
CELL11: C1.P2 (2), C2.P1 (1), D16.3 (C), D216.1 (A), D222.3 (C), JP111.2, LED12.2 (C), Q201.2 (S), R65.P2 (2), R204.1
CELL12: C1.P1 (1), D19.3 (C), D216.3 (C), JP111.1, L1.P1 (1), Q200.2 (S), R76.P2 (2)
CHRG_SHDN: R73.P1 (1); also elsewhere on the board
CSBO: JP10.P2, U3.1 (CSBO)
GND: C38.P2 (2), C41.P2 (2), C45.P2 (2), C47.P2 (2), D208.1 (A), JP10.P1, R38.P1 (1), R79.P1 (1), R208.P1 (1), R210.P1 (1), R211.P1 (1), R213.P1 (1), U3.30 (V-), U3.31 (NC); also elsewhere on the board
GPIO1: JP9.P1, R63.P1 (1), R69.P2 (2), U3.38 (GPIO1)
GPIO2: JP9.P2, R62.P2 (2), R68.P1 (1), U3.39 (GPIO2)
LOAD_SHDN: R90.P1 (1); also elsewhere on the board
unnamed: R45.P1 (1), R211.P2 (2), U3.32 (VTEMP1)
unnamed: D20.1 (A), R88.P2 (2)
unnamed: JP111.14, R41.P1 (1), R213.P2 (2), U3.33 (VTEMP2)
unnamed: C38.P1 (1), R41.P2 (2), R45.P2 (2), U3.34 (VREF)
unnamed: D1.1 (A), Q222.1 (G), R1.P2 (2)
unnamed: Q222.3 (D), R3.P2 (2), R221.2
unnamed: D2.1 (A), Q221.1 (G), R4.P2 (2)
unnamed: Q221.3 (D), R6.P2 (2), R220.2
unnamed: D4.1 (A), Q220.1 (G), R11.P2 (2)
unnamed: Q220.3 (D), R13.P2 (2), R219.2
unnamed: D5.1 (A), Q219.1 (G), R19.P2 (2)
unnamed: Q219.3 (D), R22.P2 (2), R218.2
unnamed: D7.1 (A), Q214.1 (G), R25.P2 (2)
unnamed: Q214.3 (D), R28.P2 (2), R217.2
unnamed: D8.1 (A), Q212.1 (G), R29.P2 (2)
unnamed: Q212.3 (D), R31.P2 (2), R216.2
unnamed: D10.1 (A), Q211.1 (G), R32.P2 (2)
unnamed: Q211.3 (D), R34.P2 (2), R214.2
unnamed: D11.1 (A), Q209.1 (G), R39.P2 (2)
unnamed: Q209.3 (D), R43.P2 (2), R212.2
unnamed: D12.1 (A), Q205.1 (G), R46.P2 (2)
unnamed: Q205.3 (D), R50.P2 (2), R209.2
unnamed: D14.1 (A), Q204.1 (G), R52.P2 (2)
unnamed: Q204.3 (D), R58.P2 (2), R207.2
unnamed: D16.1 (A), Q201.1 (G), R61.P2 (2)
unnamed: Q201.3 (D), R66.P2 (2), R205.2
unnamed: D19.1 (A), Q200.1 (G), R74.P2 (2)
unnamed: Q200.3 (D), R75.P2 (2), R204.2
unnamed: D208.3 (C), L1.P2 (2), R80.P1 (1)
unnamed: D15.1 (A), R73.P2 (2)
unnamed: D17.1 (A), R90.P2 (2)
unnamed: LED6.1 (A), R31.P1 (1)
unnamed: LED5.1 (A), R28.P1 (1)
unnamed: LED4.1 (A), R22.P1 (1)
unnamed: LED3.1 (A), R13.P1 (1)
unnamed: LED2.1 (A), R6.P1 (1)
unnamed: LED1.1 (A), R3.P1 (1)
unnamed: LED7.1 (A), R34.P1 (1)
unnamed: LED8.1 (A), R43.P1 (1)
unnamed: LED9.1 (A), R50.P1 (1)
unnamed: LED10.1 (A), R58.P1 (1)
unnamed: LED11.1 (A), R66.P1 (1)
unnamed: LED12.1 (A), R75.P1 (1)
S1: R1.P1 (1), U3.28 (S1)
S2: R4.P1 (1), U3.26 (S2)
S3: R11.P1 (1), U3.24 (S3)
S4: R19.P1 (1), U3.22 (S4)
S5: R25.P1 (1), U3.20 (S5)
S6: R29.P1 (1), U3.18 (S6)
S7: R32.P1 (1), U3.16 (S7)
S8: R39.P1 (1), U3.14 (S8)
S9: R46.P1 (1), U3.12 (S9)
S10: R52.P1 (1), U3.10 (S10)
S11: R61.P1 (1), U3.8 (S11)
S12: R74.P1 (1), U3.6 (S12)
SCKO: JP10.P4, U3.3 (SCKO)
SDOI: JP10.P3, U3.2 (SDOI)
SPI1_CS: R59.P1 (1), U3.44 (CSBI); also elsewhere on the board
SPI1_MISO: R64.P1 (1), U3.43 (SDO); also elsewhere on the board
SPI1_MOSI: R67.P1 (1), U3.42 (SDI); also elsewhere on the board
SPI1_SCK: R71.P1 (1), U3.41 (SCKI); also elsewhere on the board
TOS: R54.P1 (1), R210.P2 (2), U3.36 (TOS)
V+: C45.P1 (1), JP10.P5, R80.P2 (2), U3.4 (V+)
VMODE: R72.P1 (1), R208.P2 (2), U3.40 (VMODE)
VREG: C41.P1 (1), C47.P1 (1), R54.P2 (2), R59.P2 (2), R63.P2 (2), R64.P2 (2), R67.P2 (2), R68.P2 (2), R71.P2 (2), R72.P2 (2), R77.P2 (2), U3.35 (VREG)
WDTB: D15.3 (C), D17.3 (C), D20.3 (C), R77.P1 (1), R79.P2 (2), U3.37 (WDTB)

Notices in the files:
README.md:
License: MIT
